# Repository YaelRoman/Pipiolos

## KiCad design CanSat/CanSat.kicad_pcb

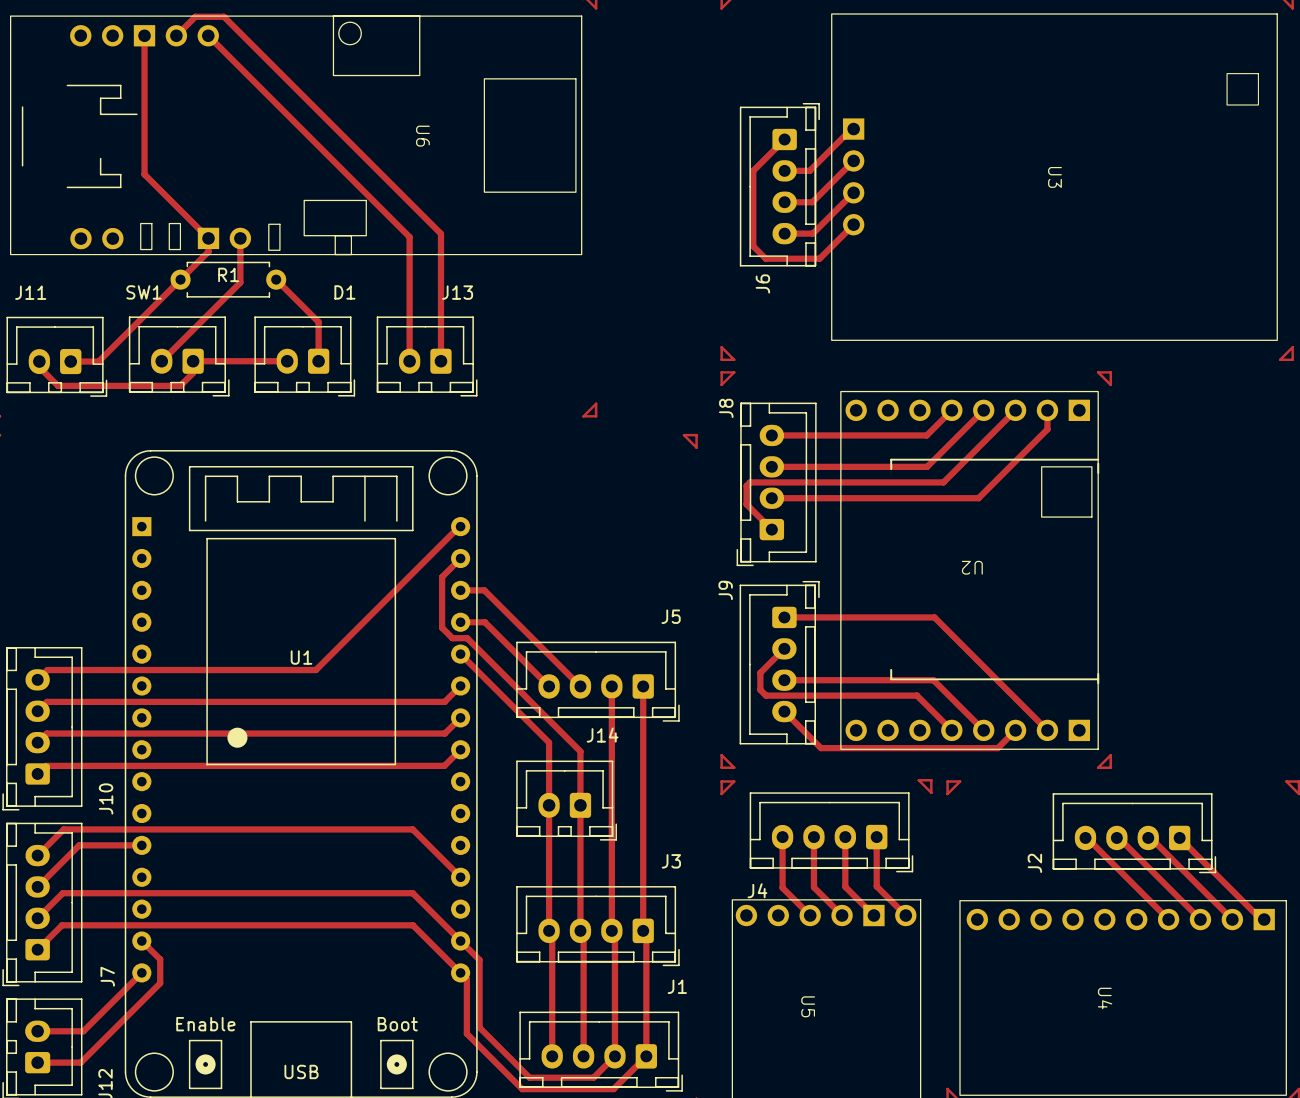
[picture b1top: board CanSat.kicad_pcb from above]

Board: 2 copper layers, 23 parts (0 on the bottom side), 40 nets.

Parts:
D1: LED_Testigo; JST_XH_B2B-XH-A_1x02_P2.50mm_Vertical
J1: MPU_XH2.54_M; JST_XH_B4B-XH-A_1x04_P2.50mm_Vertical
J2: MPU_XH2.54_H; JST_XH_B4B-XH-A_1x04_P2.50mm_Vertical
J3: BME_XH2.54_M; JST_XH_B4B-XH-A_1x04_P2.50mm_Vertical
J4: BME_XH2.54_H; JST_XH_B4B-XH-A_1x04_P2.50mm_Vertical
J5: GPS_XH2.54_M; JST_XH_B4B-XH-A_1x04_P2.50mm_Vertical
J6: GPS_XH2.54_H; JST_XH_B4B-XH-A_1x04_P2.50mm_Vertical
J7: LoRa1_XH2.54_M; JST_XH_B4B-XH-A_1x04_P2.50mm_Vertical
J8: LoRa1_XH2.54_H; JST_XH_B4B-XH-A_1x04_P2.50mm_Vertical
J9: LoRa2_XH2.54_M; JST_XH_B4B-XH-A_1x04_P2.50mm_Vertical
J10: LoRa2_XH2.54_H; JST_XH_B4B-XH-A_1x04_P2.50mm_Vertical
J11: Battery_XH2.54_M; JST_XH_B2B-XH-A_1x02_P2.50mm_Vertical
J12: Battery_XH2.54_H; JST_XH_B2B-XH-A_1x02_P2.50mm_Vertical
J13: BatteryI2C_XH2.54_M; JST_XH_B2B-XH-A_1x02_P2.50mm_Vertical
J14: BatteryI2C_XH2.54_H; JST_XH_B2B-XH-A_1x02_P2.50mm_Vertical
R1: R_330Ohm; R_Axial_DIN0207_L6.3mm_D2.5mm_P7.62mm_Horizontal
SW1: SW_Power; JST_XH_B2B-XH-A_1x02_P2.50mm_Vertical
U1: ESP32_DevKit_V1; esp32_devkit_v1_doit
U2: LoRa Ra-02
U3: NEO6MV2 GPS; NE06MV2 GPS
U4: MPU-6500
U5: BME280
U6: LiPoBoostI2C

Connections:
GPS.RX: J5.4, U1.27 (RXD0/IO3)
GPS.TX: J5.3, U1.28 (TXD0/IO1)
LoRa1.DI00: J7.4, U1.19 (IO2)
LoRa1.RST: J7.3, U1.11 (IO14)
LoRa2.MISO: J10.3, U1.25 (IO19)
LoRa2.MOSI: J10.4, U1.30 (IO23)
LoRa2.NSS: J10.1, U1.23 (IO5)
LoRa2.SCK: J10.2, U1.24 (IO18)
MPU.GND: J1.2, J3.2, J5.2, J7.2, U1.17 (GND)
MPU.SCL: J1.3, J3.3, J14.1, U1.29 (IO22)
MPU.SDA: J1.4, J3.4, J14.2, U1.26 (IO21)
MPU.VCC: J1.1, J3.1, J5.1, J7.1, U1.16 (3V3)
unnamed: D1.2 (A), J11.2, SW1.1
unnamed: D1.1 (K), R1.2
unnamed: J2.1, U4.1 (VCC)
unnamed: J2.2, U4.2 (GND)
unnamed: J2.3, U4.3 (SCL)
unnamed: J2.4, U4.4 (SDA)
unnamed: J4.1, U5.1 (VCC)
unnamed: J4.2, U5.2 (GND)
unnamed: J4.3, U5.3 (SCL)
unnamed: J4.4, U5.4 (SDA)
unnamed: J6.1, U3.4 (VCC)
unnamed: J6.2, U3.1 (GND)
unnamed: J6.3, U3.2 (TX)
unnamed: J6.4, U3.3 (RX)
unnamed: J8.1, U2.3 (3.3V)
unnamed: J8.2, U2.2 (GND)
unnamed: J8.3, U2.4 (RST)
unnamed: J8.4, U2.5 (DI00)
unnamed: J9.1, U2.10 (NSS)
unnamed: J9.2, U2.13 (SCK)
unnamed: J9.3, U2.12 (MISO)
unnamed: J9.4, U2.11 (MOSI)
unnamed: J11.1, R1.1, U6.3 (GND), U6.7 (GND)
unnamed: J12.1, U1.14 (GND)
unnamed: J12.2, U1.15 (VIN)
unnamed: J13.1, U6.2 (SCL)
unnamed: J13.2, U6.1 (SDA)
unnamed: SW1.2, U6.6 (VOUT)

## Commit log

2025-09-23 2nd commit
2025-09-23 Adde my library
2025-09-24 Updated schematic and added footprints
2025-09-26 Change schemes and footprints
2025-09-30 PCBv1
2025-10-06 Agrega PDF
2025-10-15 Beta version 1.0
2025-10-18 .ino code
